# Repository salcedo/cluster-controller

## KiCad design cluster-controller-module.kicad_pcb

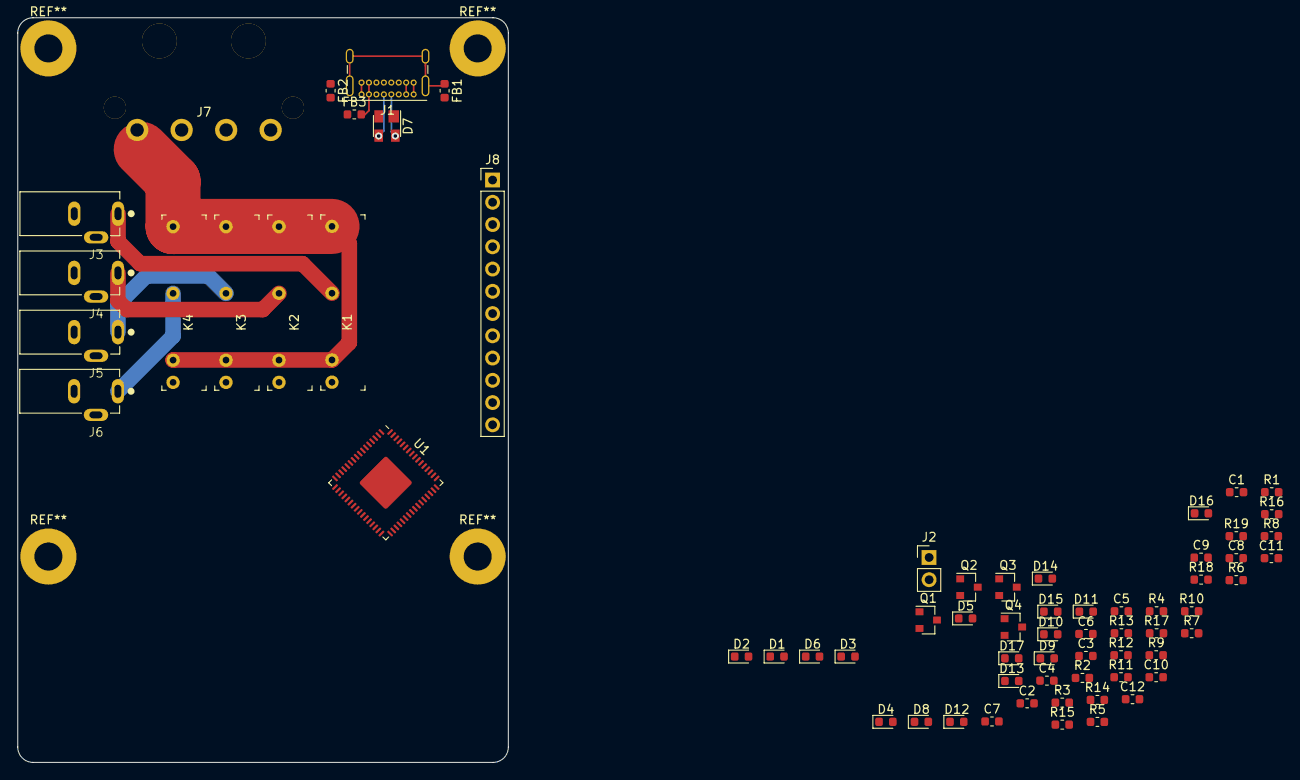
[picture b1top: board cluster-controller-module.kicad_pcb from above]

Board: 4 copper layers, 56.0 x 85.0 mm, 68 parts (0 on the bottom side), 56 nets.

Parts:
C1, C3, C5, C6, C9, C11: 0.1uF; C_0603_1608Metric
C2, C4, C7, C8, C10, C12: 4.7uF; C_0603_1608Metric
D1: TX0; LED_0603_1608Metric
D2: RX0; LED_0603_1608Metric
D3: TX1; LED_0603_1608Metric
D4: RX1; LED_0603_1608Metric
D5: TX2; LED_0603_1608Metric
D6: RX2; LED_0603_1608Metric
D7: SP0503BAHT; SOT-143
D8: TX3; LED_0603_1608Metric
D9: RX3; LED_0603_1608Metric
D10: ST0; LED_0603_1608Metric
D11: ST1; LED_0603_1608Metric
D12: ST2; LED_0603_1608Metric
D13: ST3; LED_0603_1608Metric
D14, D15, D16, D17: 1N4148; D_0603_1608Metric
FB1, FB2, FB3: BD; L_0603_1608Metric
J1: USB_C_Receptacle_USB2.0; USB_C_Receptacle_GCT_USB4085
J2: VBUS_POWER; PinHeader_1x02_P2.54mm_Vertical
J3, J4, J5, J6: PJ-007; CUI_PJ-007
J7: 641737-1
J8: UART; PinHeader_1x12_P2.54mm_Vertical
K1, K2, K3, K4: G6DN-DC5; G6DN-1A-DC5
Q1, Q2, Q3, Q4: BHS105; SOT-23
R1, R2, R3, R5, R7, R8, R9, R10, R12, R13, R14, R15: 1K; R_0603_1608Metric
R4, R6: 5.1K; R_0603_1608Metric
R11: 4.7K; R_0603_1608Metric
R16, R17, R18, R19: 10K; R_0603_1608Metric
U1: CP2108; QFN-64-1EP_9x9mm_P0.5mm_EP4.35x4.35mm

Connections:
+5V: C11.1, C12.1, D14.1, D15.1, D16.1, D17.1, J2.2, J7.4, K1.2, K1.8, K2.2, K2.8, K3.2, K3.8, K4.2, K4.8, U1.60
/D+: D7.4, J1.A6, J1.B6, U1.62
/D-: D7.3, J1.A7, J1.B7, U1.63
/LED_RX0: D2.1, U1.40
/LED_RX1: D4.1, U1.33
/LED_RX2: D6.1, U1.29
/LED_RX3: D9.1, U1.23
/LED_ST_A: D10.1, U1.37
/LED_ST_B: D11.1, U1.31
/LED_ST_C: D12.1, U1.27
/LED_ST_D: D13.1, U1.21
/LED_TX0: D1.1, U1.41
/LED_TX1: D3.1, U1.34
/LED_TX2: D5.1, U1.30
/LED_TX3: D8.1, U1.26
/RELAY_A: Q1.1, R16.1, U1.38
/RELAY_B: Q2.1, R17.1, U1.32
/RELAY_C: Q3.1, R18.1, U1.28
/RELAY_D: Q4.1, R19.1, U1.22
/RX0: J8.2, U1.56
/RX1: J8.5, U1.48
/RX2: J8.8, U1.15
/RX3: J8.11, U1.1
/TX0: J8.1, U1.57
/TX1: J8.4, U1.49
/TX2: J8.7, U1.16
/TX3: J8.10, U1.4
/VBUS: C5.1, C7.1, FB3.1, J2.1, U1.61
GND: C1.2, C2.2, C3.2, C4.2, C5.2, C6.2, C7.2, C8.2, C9.2, C10.2, C11.2, C12.2, D7.1, FB1.2, FB2.2, J3.2, J3.3, J4.2, J4.3, J5.2, J5.3, J6.2, J6.3, J7.2, J7.3, J8.3, J8.6, J8.9, J8.12, Q1.2, Q2.2, Q3.2, Q4.2, R4.2, R6.2, R16.2, R17.2, R18.2, R19.2, U1.2, U1.25, U1.59
unnamed: D1.2, R1.2
unnamed: D2.2, R2.2
unnamed: D3.2, R3.2
unnamed: D4.2, R5.2
unnamed: D5.2, R7.2
unnamed: D6.2, R8.2
unnamed: D8.2, R9.2
unnamed: D9.2, R10.2
unnamed: D10.2, R12.2
unnamed: D11.2, R13.2
unnamed: D12.2, R14.2
unnamed: D13.2, R15.2
unnamed: D14.2, K1.1, Q1.3
unnamed: D15.2, K2.1, Q2.3
unnamed: D16.2, K3.1, Q3.3
unnamed: D17.2, K4.1, Q4.3
unnamed: FB1.1, J1.S1
unnamed: FB2.1, J1.A1, J1.A12, J1.B1, J1.B12
unnamed: FB3.2, J1.A4, J1.A9, J1.B4, J1.B9
unnamed: J1.A5, R6.1
unnamed: J1.B5, R4.1
unnamed: J3.1, K1.5
unnamed: J4.1, K2.5
unnamed: J5.1, K3.5
unnamed: J6.1, K4.5
unnamed: R11.2, U1.64
VDD: C1.1, C2.1, C3.1, C4.1, C6.1, C8.1, C9.1, C10.1, R1.1, R2.1, R3.1, R5.1, R7.1, R8.1, R9.1, R10.1, R11.1, R12.1, R13.1, R14.1, R15.1, U1.3, U1.24, U1.39, U1.58

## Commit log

2024-10-27 for archive
